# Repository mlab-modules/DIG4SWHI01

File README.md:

# DIG4SWHI01A - quad channel current sensing high-side switch

Switch for voltage from 4 V to 28 V. Resistance in spliced state 50 mOhm. Integrated circuit [VNQ7050AJ](https://www.st.com/en/automotive-analog-and-power/vnq7050aj.html).

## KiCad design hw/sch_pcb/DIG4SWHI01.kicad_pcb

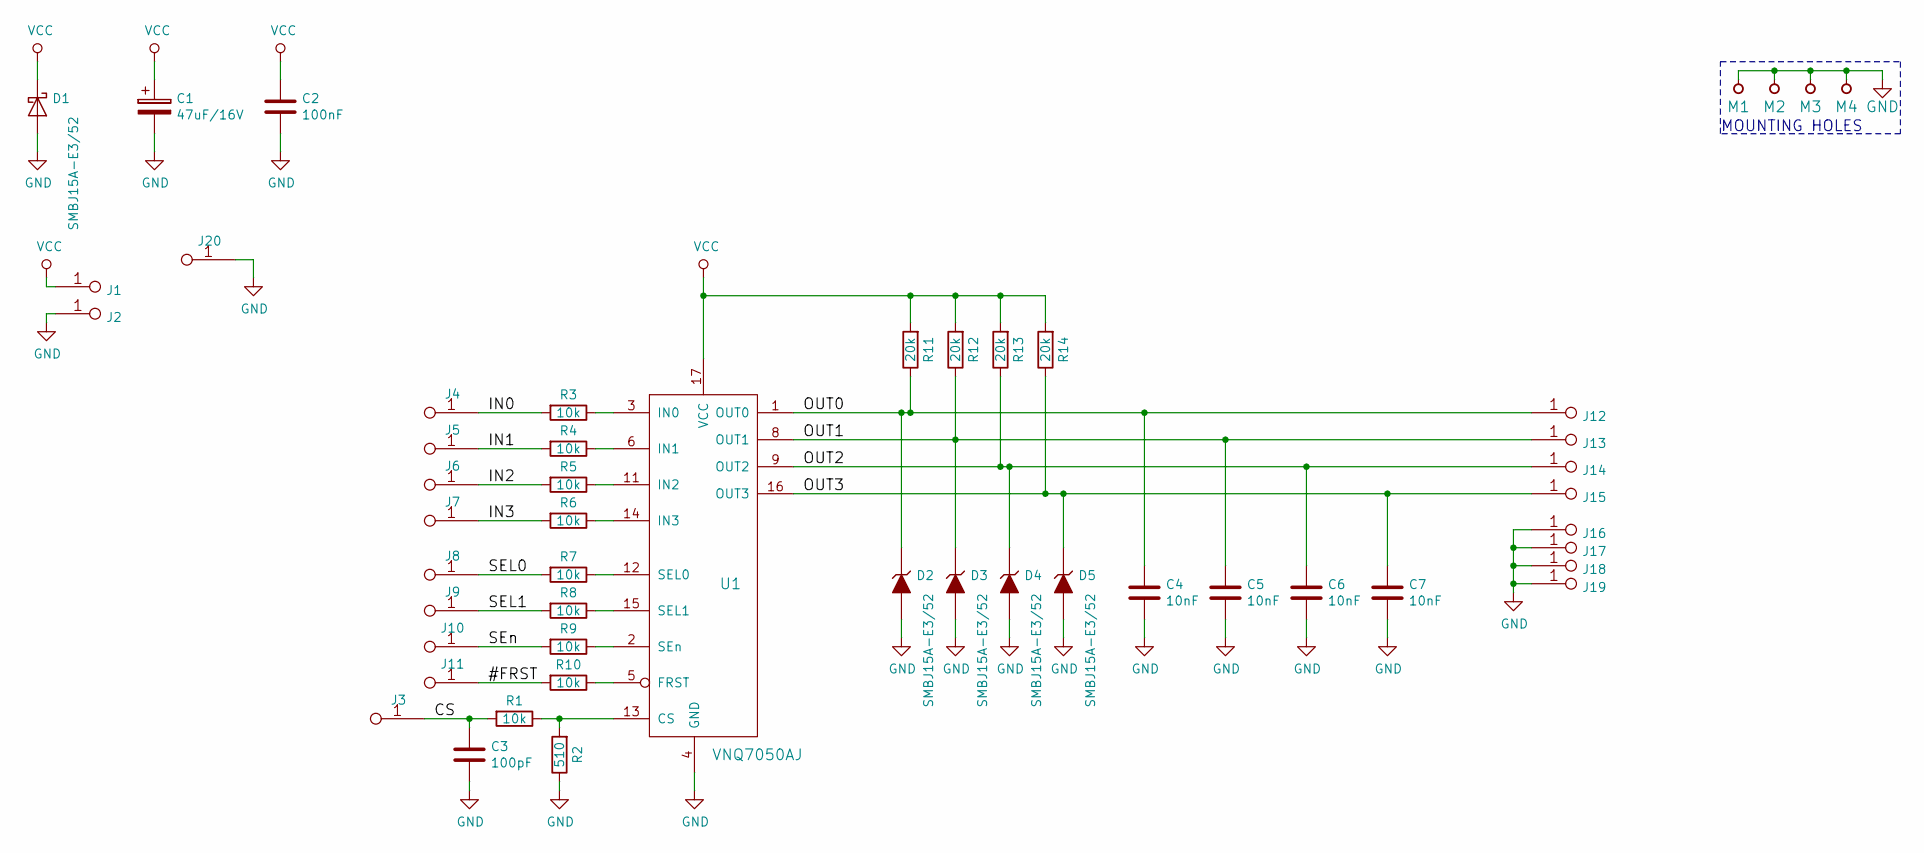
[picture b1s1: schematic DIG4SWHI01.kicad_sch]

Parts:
C1: 47uF/16V; TantalC_SizeC_Reflow
C2: 100nF; SMD-0805
C3: 100pF; SMD-0805
C4, C5, C6, C7: 10nF; SMD-0805
D1: SMBJ15A-E3/52; Diode-SMB_Standard
D2, D3, D4, D5: SMBJ15A-E3/52; SMB_Standard
J1, J2, J12, J13, J14, J15, J16, J17, J18, J19: CONN1_1; WAGO256_2
J3, J4, J5, J6, J7, J8, J9, J10, J11, J20: JUMP_2x1; Straight_2x01
M1, M2, M3, M4: HOLE; MountingHole_3mm
R1, R3, R4, R5, R6, R7, R8, R9, R10: 10k; SMD-0805
R2: 510; SMD-0805
R11, R12, R13, R14: 20k; SMD-0805
U1: VNQ7050AJ; PowerSSO-16

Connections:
/#FRST: J11.1, J11.2 (1), R10.2
/CS: C3.1, J3.1, J3.2 (1), R1.2
/IN0: J4.1, J4.2 (1), R3.2
/IN1: J5.1, J5.2 (1), R4.2
/IN2: J6.1, J6.2 (1), R5.2
/IN3: J7.1, J7.2 (1), R6.2
/OUT0: C4.1, D2.1 (K), J12.1, R11.1, U1.1 (OUT0)
/OUT1: C5.1, D3.1 (K), J13.1, R12.1, U1.8 (OUT1)
/OUT2: C6.1, D4.1 (K), J14.1, R13.1, U1.9 (OUT2)
/OUT3: C7.1, D5.1 (K), J15.1, R14.1, U1.16 (OUT3)
/SEL0: J8.1, J8.2 (1), R7.2
/SEL1: J9.1, J9.2 (1), R8.2
/SEn: J10.1, J10.2 (1), R9.2
GND: C1.2, C2.2, C3.2, C4.2, C5.2, C6.2, C7.2, D1.2 (A), D2.2 (A), D3.2 (A), D4.2 (A), D5.2 (A), J2.1, J16.1, J17.1, J18.1, J19.1, J20.1, J20.2 (1), M1.1, M2.1, M3.1, M4.1, R2.1, U1.4 (GND)
unnamed: R1.1, R2.2, U1.13 (CS)
unnamed: R10.1, U1.5 (FRST)
unnamed: R3.1, U1.3 (IN0)
unnamed: R4.1, U1.6 (IN1)
unnamed: R5.1, U1.11 (IN2)
unnamed: R6.1, U1.14 (IN3)
unnamed: R7.1, U1.12 (SEL0)
unnamed: R8.1, U1.15 (SEL1)
unnamed: R9.1, U1.2 (SEn)
VCC: C1.1, C2.1, D1.1 (K), J1.1, R11.2, R12.2, R13.2, R14.2, U1.17 (VCC)

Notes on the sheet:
MOUNTING HOLES

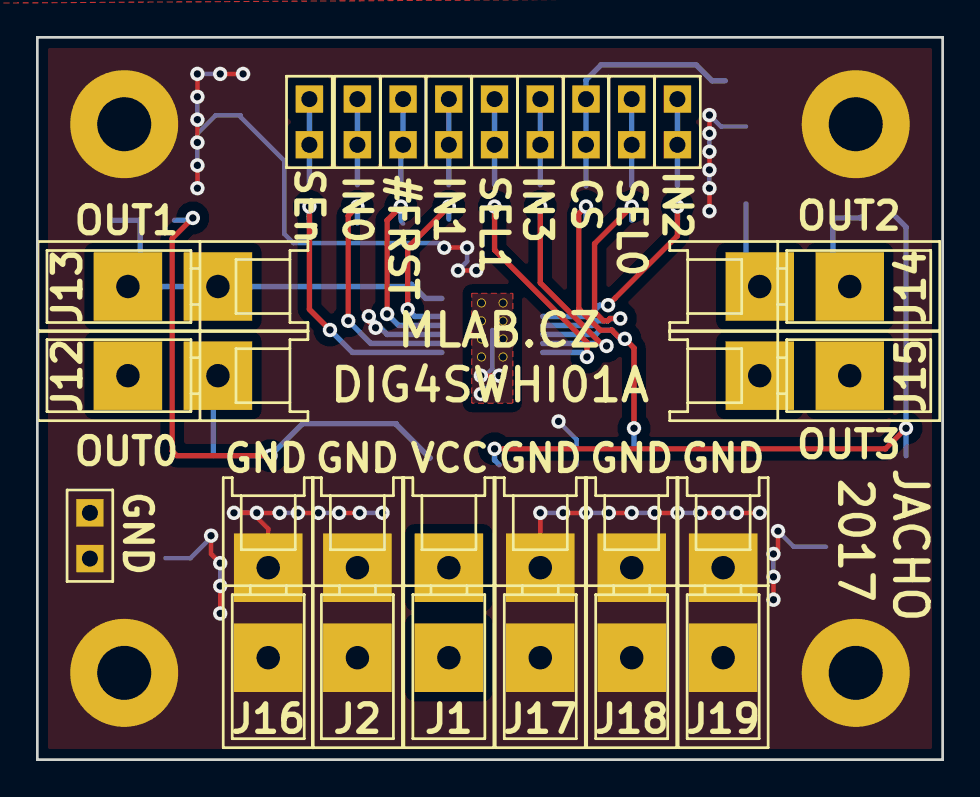
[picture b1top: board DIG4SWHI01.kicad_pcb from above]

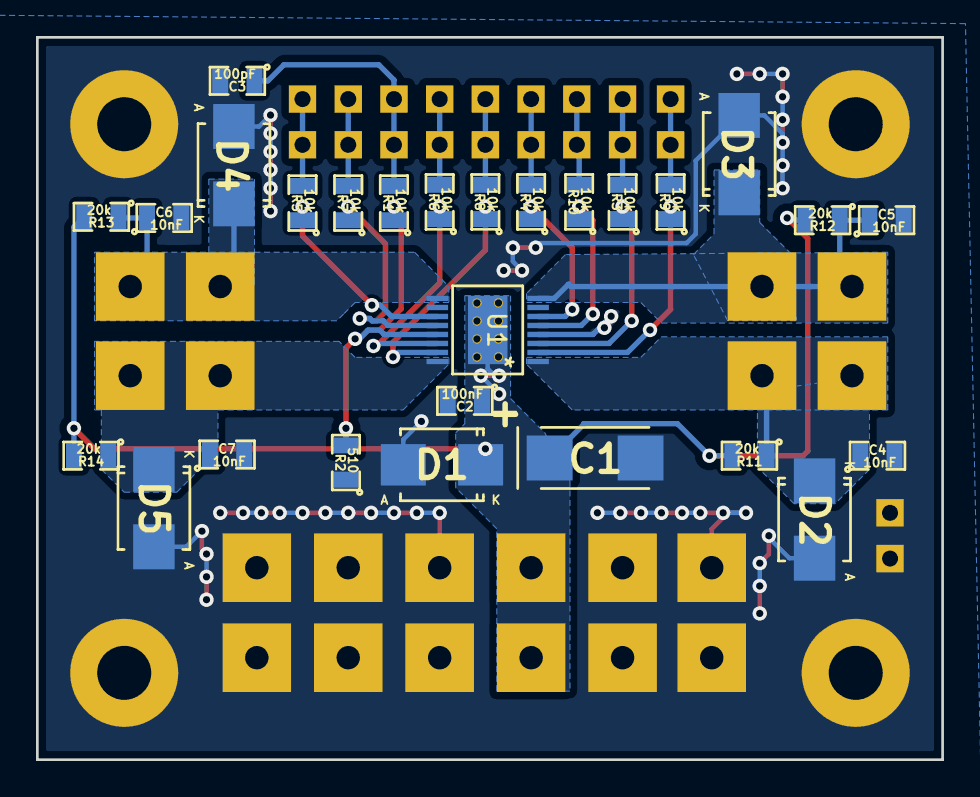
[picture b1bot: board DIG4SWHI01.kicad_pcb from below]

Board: 2 copper layers, 50.3 x 40.1 mm, 51 parts (27 on the bottom side), 24 nets.

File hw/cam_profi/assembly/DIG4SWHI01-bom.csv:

Component,Description,Part,References,Value,Footprint,Quantity Per PCB,Datasheet
1,,C,C3,100pF,SMD-0805,1,
2,,C,C4C5C6C7,10nF,SMD-0805,4,
3,,C,C2,100nF,SMD-0805,1,
4,,CP,C1,47uF/16V,TantalC_SizeC_Reflow,1,
5,,D_Schottky,D1,SMBJ15A-E3/52,Diode-SMB_Standard,1,
6,,D_ZENER,D2D3D4D5,SMBJ15A-E3/52,SMB_Standard,4,
7,,CONN1_1,J1J2J12J13J14J15J16J17J18J19,CONN1_1,WAGO256_2,10,
8,,JUMP_2x1,J3J4J5J6J7J8J9J10J11J20,JUMP_2x1,Straight_2x01,10,
9,,R,R2,510,SMD-0805,1,
10,,R,R1R3R4R5R6R7R8R9R10,10k,SMD-0805,9,
11,,R,R11R12R13R14,20k,SMD-0805,4,
12,,VNQ7050AJ,U1,VNQ7050AJ,PowerSSO-16,1,

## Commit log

2023-04-01 Adding force option to enable splitting in not fresh copy of Modules repository.
2023-09-17 automated commit; add github actions
2023-09-17 Update workflow files
2023-09-17 Update metadata files
2024-05-18 Update project according to actual MLAB standard.
2024-05-18 Attempt to resolve action fail.
2024-05-31 Update actions products
